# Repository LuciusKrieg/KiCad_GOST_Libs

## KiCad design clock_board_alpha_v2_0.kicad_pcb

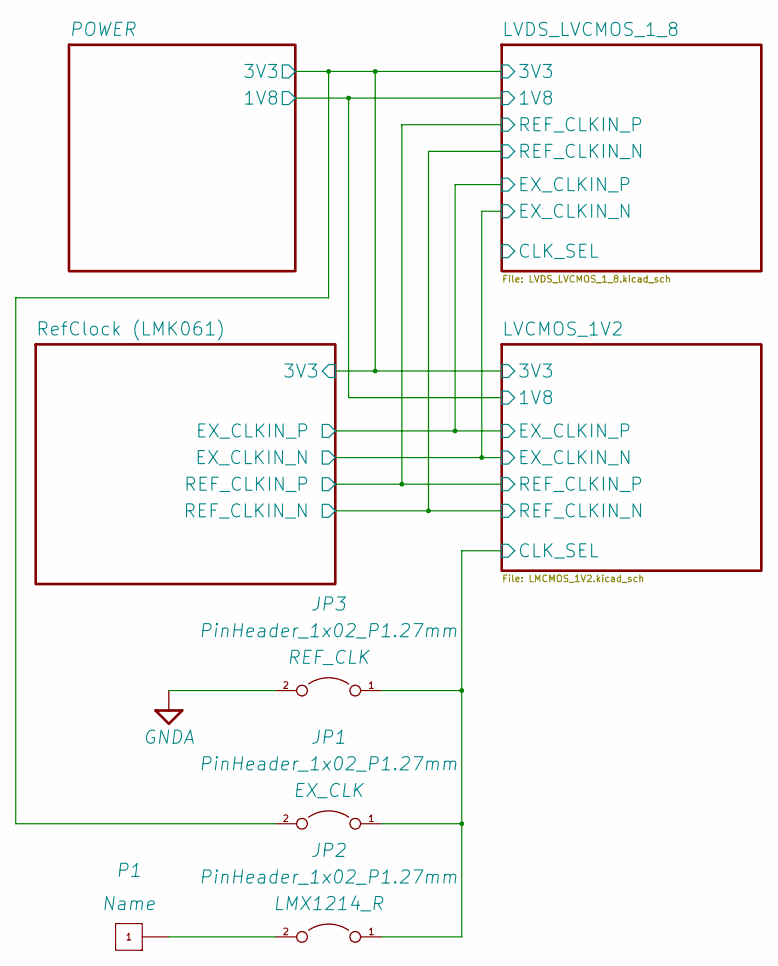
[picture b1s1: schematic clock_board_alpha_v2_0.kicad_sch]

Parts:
JP1, JP2, JP3: PinHeader_1x02_P1.27mm; PinHeader_1x02_P1.27mm_Vertical
P1: PinHeader_1x01_P1.00mm_Vertical

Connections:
/LVCMOS_1V2/CLK_SEL: JP1.1 (A), JP2.1 (A), JP3.1 (A); also elsewhere on the board
GNDA: JP3.2 (B); also elsewhere on the board
unnamed: JP2.2 (B), P1.1
VDD_3V3: JP1.2 (B); also elsewhere on the board

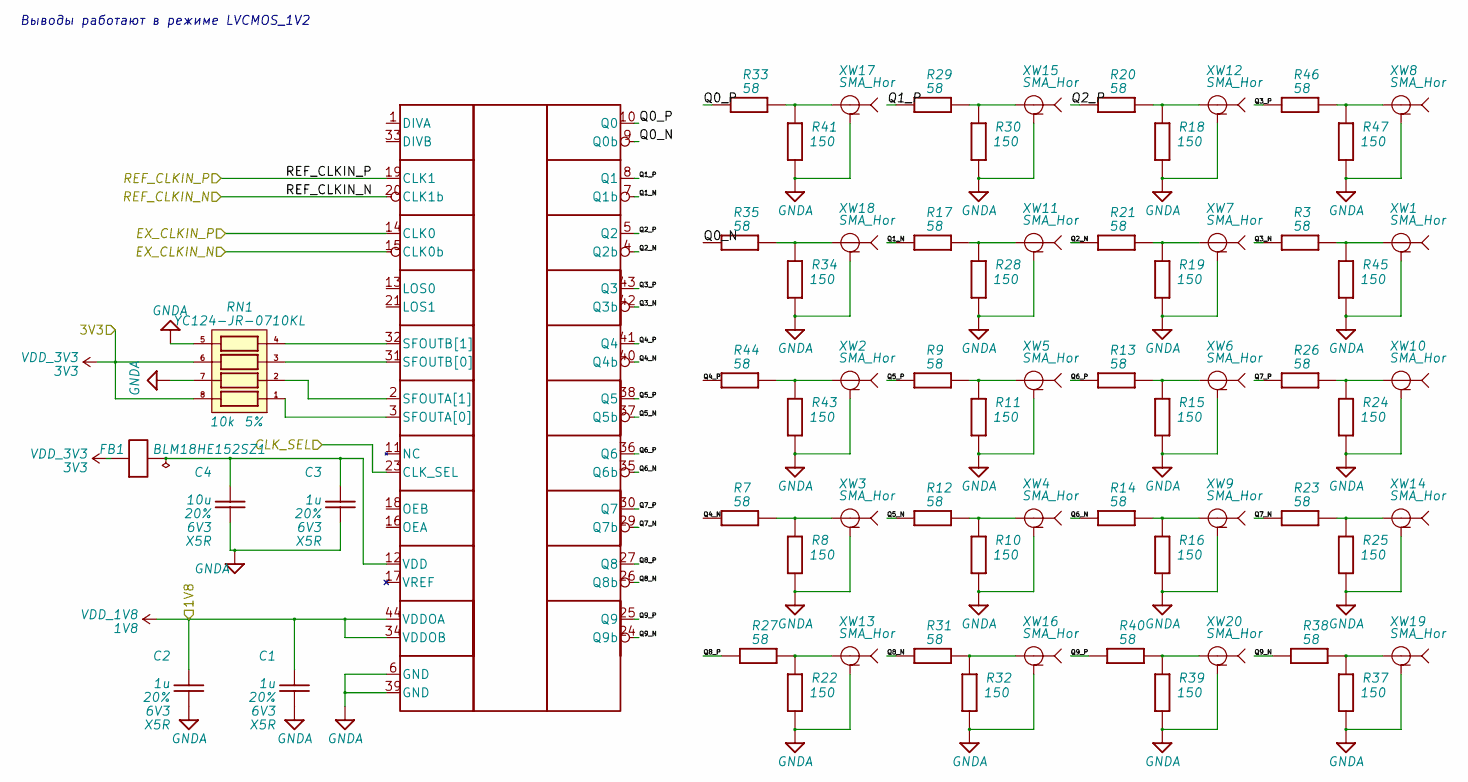
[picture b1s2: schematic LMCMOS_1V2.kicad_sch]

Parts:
C1, C2, C3: GRM033R60J105MEA; C_0201_0603Metric; Tolerance 20%
C4: CL05A106MQ5NUNC; C_0402_1005Metric; Tolerance 20%
FB1: BLM18HE152SZ1; L_0603_1608Metric
R3, R7, R8, R9, R10, R11, R12, R13, R14, R15, R16, R17, R18, R19, R20, R21, R22, R23, R24, R25, R26, R27, R28, R29, R30, R31, R32, R33, R34, R35, R37, R38, R39, R40, R41, R43, R44, R45, R46, R47: TNPR020150R0FEED; R_0201_0603Metric; Tolerance 1%
RN1: YC124-JR-0710KL; R_Array_Convex_4x0402; Tolerance 5%
SI53302: TQFN-44-1EP_7x7mm_P0.5mm_EP4.7x4.7mm
XW1, XW2, XW3, XW4, XW5, XW6, XW7, XW8, XW9, XW10, XW11, XW12, XW13, XW14, XW15, XW16, XW17, XW18, XW19, XW20: SMA_Amphenol_901-143_Horizontal

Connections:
/LVCMOS_1V2/CLK_SEL: SI53302.23 (CLK_SEL); also elsewhere on the board
/LVCMOS_1V2/Q0_N: R35.2, SI53302.9 (Q0b)
/LVCMOS_1V2/Q0_P: R33.2, SI53302.10 (Q0)
/LVCMOS_1V2/Q1_N: R17.2, SI53302.7 (Q1b)
/LVCMOS_1V2/Q1_P: R29.2, SI53302.8 (Q1)
/LVCMOS_1V2/Q2_N: R21.2, SI53302.4 (Q2b)
/LVCMOS_1V2/Q2_P: R20.2, SI53302.5 (Q2)
/LVCMOS_1V2/Q3_N: R3.2, SI53302.42 (Q3b)
/LVCMOS_1V2/Q3_P: R46.2, SI53302.43 (Q3)
/LVCMOS_1V2/Q4_N: R7.2, SI53302.40 (Q4b)
/LVCMOS_1V2/Q4_P: R44.2, SI53302.41 (Q4)
/LVCMOS_1V2/Q5_N: R12.2, SI53302.37 (Q5b)
/LVCMOS_1V2/Q5_P: R9.2, SI53302.38 (Q5)
/LVCMOS_1V2/Q6_N: R14.2, SI53302.35 (Q6b)
/LVCMOS_1V2/Q6_P: R13.2, SI53302.36 (Q6)
/LVCMOS_1V2/Q7_N: R23.2, SI53302.29 (Q7b)
/LVCMOS_1V2/Q7_P: R26.2, SI53302.30 (Q7)
/LVCMOS_1V2/Q8_N: R31.2, SI53302.26 (Q8b)
/LVCMOS_1V2/Q8_P: R27.2, SI53302.27 (Q8)
/LVCMOS_1V2/Q9_N: R38.2, SI53302.24 (Q9b)
/LVCMOS_1V2/Q9_P: R40.2, SI53302.25 (Q9)
/LVCMOS_1V2/REF_CLKIN_N: SI53302.20 (CLK1b); also elsewhere on the board
/LVCMOS_1V2/REF_CLKIN_P: SI53302.19 (CLK1); also elsewhere on the board
/RefClock (LMK061)/EX_CLKIN_N: SI53302.15 (CLK0b); also elsewhere on the board
/RefClock (LMK061)/EX_CLKIN_P: SI53302.14 (CLK0); also elsewhere on the board
GNDA: C1.2, C2.2, C3.2, C4.2, R8.1, R10.1, R11.1, R15.1, R16.1, R18.1, R19.1, R22.1, R24.1, R25.1, R28.1, R30.1, R32.1, R34.1, R37.1, R39.1, R41.1, R43.1, R45.1, R47.1, RN1.5, RN1.7, SI53302.6 (GND), SI53302.39 (GND), XW1.2, XW2.2, XW3.2, XW4.2, XW5.2, XW6.2, XW7.2, XW8.2, XW9.2, XW10.2, XW11.2, XW12.2, XW13.2, XW14.2, XW15.2, XW16.2, XW17.2, XW18.2, XW19.2, XW20.2; also elsewhere on the board
unnamed: R3.1, R45.2, XW1.1
unnamed: R7.1, R8.2, XW3.1
unnamed: R10.2, R12.1, XW4.1
unnamed: R9.1, R11.2, XW5.1
unnamed: R13.1, R15.2, XW6.1
unnamed: R14.1, R16.2, XW9.1
unnamed: R17.1, R28.2, XW11.1
unnamed: R18.2, R20.1, XW12.1
unnamed: R19.2, R21.1, XW7.1
unnamed: R22.2, R27.1, XW13.1
unnamed: R23.1, R25.2, XW14.1
unnamed: R24.2, R26.1, XW10.1
unnamed: R29.1, R30.2, XW15.1
unnamed: R31.1, R32.2, XW16.1
unnamed: R33.1, R41.2, XW17.1
unnamed: R34.2, R35.1, XW18.1
unnamed: R37.2, R38.1, XW19.1
unnamed: R39.2, R40.1, XW20.1
unnamed: R43.2, R44.1, XW2.1
unnamed: R46.1, R47.2, XW8.1
unnamed: RN1.1, SI53302.3 (SFOUTA[0])
unnamed: RN1.2, SI53302.2 (SFOUTA[1])
unnamed: RN1.3, SI53302.31 (SFOUTB[0])
unnamed: RN1.4, SI53302.32 (SFOUTB[1])
unnamed: C3.1, C4.1, FB1.2, SI53302.12 (VDD)
VDD_1V8: C1.1, C2.1, SI53302.34 (VDDOB), SI53302.44 (VDDOA); also elsewhere on the board
VDD_3V3: FB1.1, RN1.6, RN1.8; also elsewhere on the board

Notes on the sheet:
Выводы работают в режиме LVСMOS_1V2

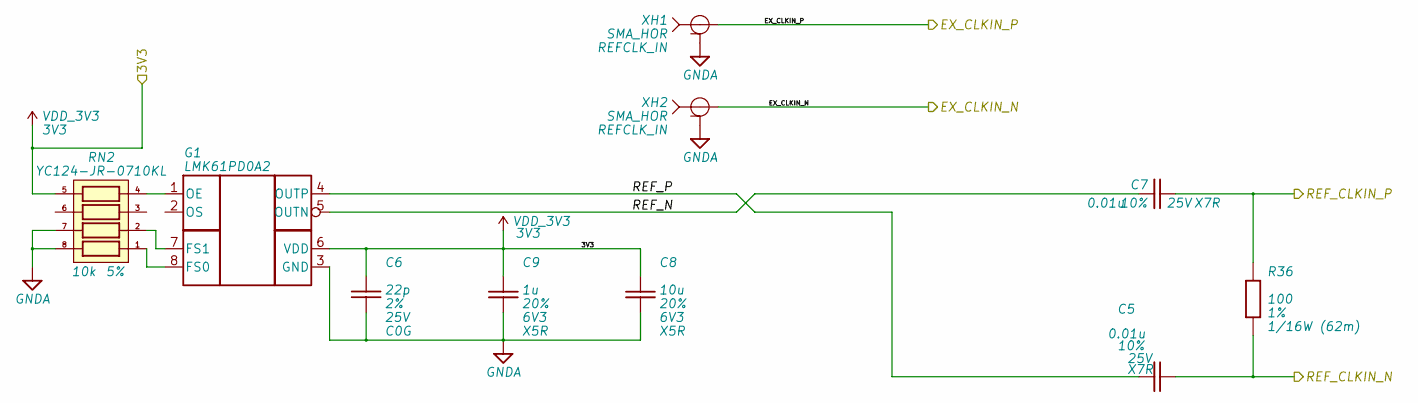
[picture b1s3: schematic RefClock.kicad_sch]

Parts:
C5, C7: GRM033R71E103KE; C_0201_0603Metric; Tolerance 10%
C6: GJM0335C1E220GB; C_0201_0603Metric; Tolerance 2%
C8: CL05A106MQ5NUNC; C_0402_1005Metric; Tolerance 20%
C9: GRM033R60J105MEA; C_0201_0603Metric; Tolerance 20%
G1: LMK61PD0A2; QFM-8-SIA
R36: RC0402FR-07100RL; R_0402_1005Metric; Tolerance 1%
RN2: YC124-JR-0710KL; R_Array_Convex_4x0402; Tolerance 5%
XH1, XH2: SMA_HOR; SMA_Amphenol_901-144_Vertical

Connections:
/LVCMOS_1V2/REF_CLKIN_N: C5.2, R36.1; also elsewhere on the board
/LVCMOS_1V2/REF_CLKIN_P: C7.2, R36.2; also elsewhere on the board
/RefClock (LMK061)/EX_CLKIN_N: XH2.1; also elsewhere on the board
/RefClock (LMK061)/EX_CLKIN_P: XH1.1; also elsewhere on the board
/RefClock (LMK061)/REF_N: C7.1, G1.5 (OUTN)
/RefClock (LMK061)/REF_P: C5.1, G1.4 (OUTP)
GNDA: C6.1, C8.2, C9.2, G1.3 (GND), RN2.7, RN2.8, XH1.2, XH2.2; also elsewhere on the board
unnamed: G1.8 (FS0), RN2.1
unnamed: G1.7 (FS1), RN2.2
unnamed: G1.1 (OE), RN2.4
VDD_3V3: C6.2, C8.1, C9.1, G1.6 (VDD), RN2.5; also elsewhere on the board

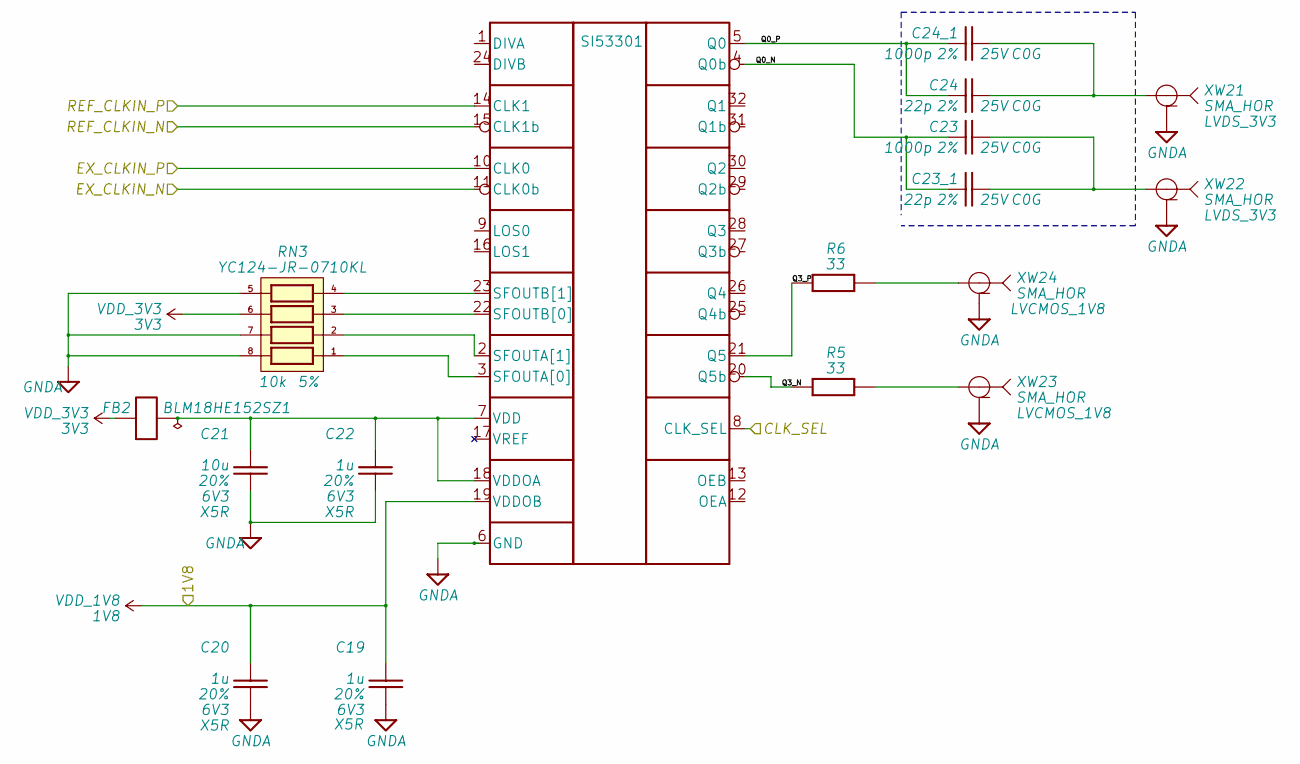
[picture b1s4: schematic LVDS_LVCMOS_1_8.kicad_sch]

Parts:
C19, C20, C22: GRM033R60J105MEA; C_0201_0603Metric; Tolerance 20%
C21: CL05A106MQ5NUNC; C_0402_1005Metric; Tolerance 20%
C23, C24_1: GRM0335C1E102GA; C_0201_0603Metric; Tolerance 2%
C23_1, C24: GJM0335C1E220GB; C_0201_0603Metric; Tolerance 2%
FB2: BLM18HE152SZ1; L_0603_1608Metric
R5, R6: TNPR020150R0FEED; R_0201_0603Metric; Tolerance 1%
RN3: YC124-JR-0710KL; R_Array_Convex_4x0402; Tolerance 5%
SI53301: QFN-32-1EP_5x5mm_P0.5mm_EP3.1x3.1mm
XW21, XW22, XW23, XW24: SMA_HOR; SMA_Amphenol_901-143_Horizontal

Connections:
/LVCMOS_1V2/REF_CLKIN_N: SI53301.15 (CLK1b); also elsewhere on the board
/LVCMOS_1V2/REF_CLKIN_P: SI53301.14 (CLK1); also elsewhere on the board
/LVDS_LVCMOS_1_8/CLK_SEL: SI53301.8 (CLK_SEL)
/LVDS_LVCMOS_1_8/Q0_N: C23.1, C23_1.1, SI53301.4 (Q0b)
/LVDS_LVCMOS_1_8/Q0_P: C24.1, C24_1.1, SI53301.5 (Q0)
/LVDS_LVCMOS_1_8/Q3_N: R5.2, SI53301.20 (Q5b)
/LVDS_LVCMOS_1_8/Q3_P: R6.2, SI53301.21 (Q5)
/RefClock (LMK061)/EX_CLKIN_N: SI53301.11 (CLK0b); also elsewhere on the board
/RefClock (LMK061)/EX_CLKIN_P: SI53301.10 (CLK0); also elsewhere on the board
GNDA: C19.2, C20.2, C21.2, C22.2, RN3.5, RN3.7, RN3.8, SI53301.6 (GND), XW21.2, XW22.2, XW23.2, XW24.2; also elsewhere on the board
unnamed: C23.2, C23_1.2, XW22.1
unnamed: C24.2, C24_1.2, XW21.1
unnamed: R5.1, XW23.1
unnamed: R6.1, XW24.1
unnamed: RN3.1, SI53301.3 (SFOUTA[0])
unnamed: RN3.2, SI53301.2 (SFOUTA[1])
unnamed: RN3.3, SI53301.22 (SFOUTB[0])
unnamed: RN3.4, SI53301.23 (SFOUTB[1])
unnamed: C21.1, C22.1, FB2.2, SI53301.7 (VDD), SI53301.18 (VDDOA)
VDD_1V8: C19.1, C20.1, SI53301.19 (VDDOB); also elsewhere on the board
VDD_3V3: FB2.1, RN3.6; also elsewhere on the board

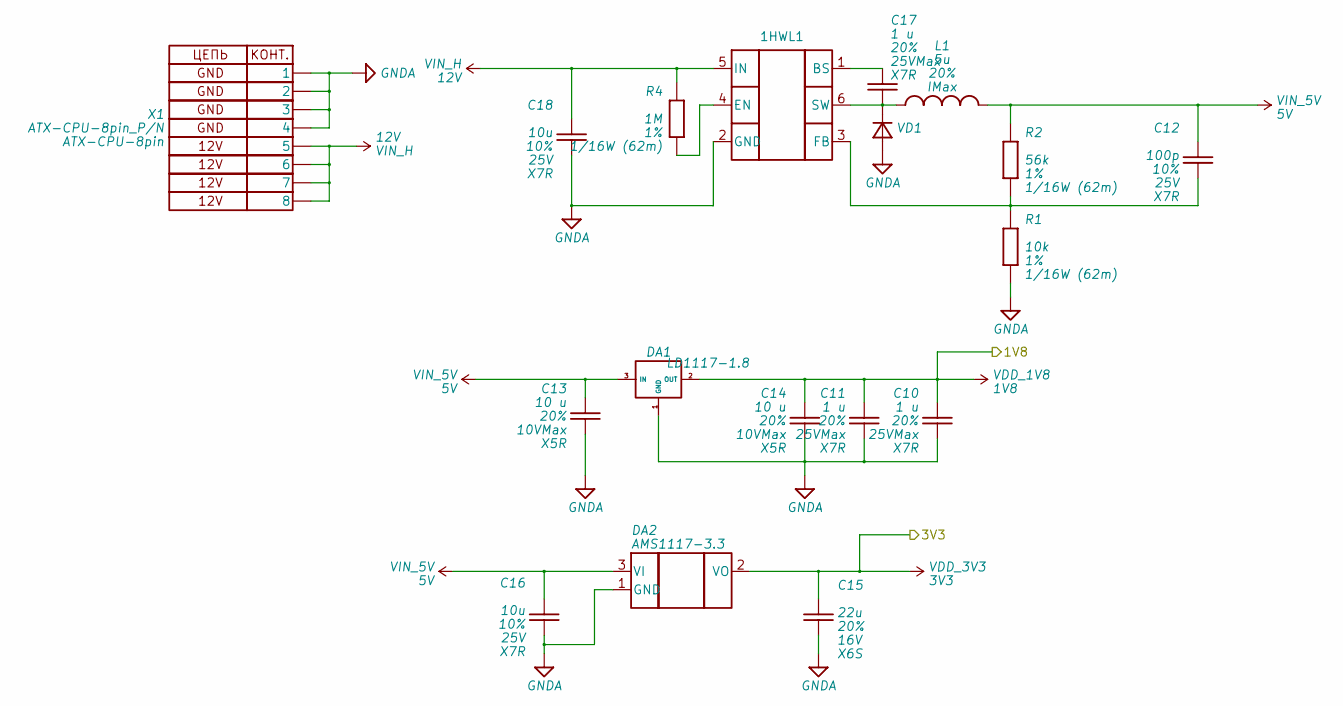
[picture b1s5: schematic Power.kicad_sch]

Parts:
1HWL1: SOT-23-6
C10, C11, C17: GRM155R61E105KA12D; C_0201_0603Metric; Tolerance 20%
C12, C16, C18: CL21B106KAYQNN; C_0805_2012Metric; Tolerance 10%
C13, C14: CL05A106MP5NUNC; C_0402_1005Metric; Tolerance 20%
C15: GRM21BC81C226ME44; C_0805_2012Metric; Tolerance 20%
DA1: LD1117-1.8; SOT-223-3_TabPin2
DA2: AMS1117-3.3; SOT-223-3_TabPin2
L1: L_Wuerth_HCI-5040; Tolerance 20%
R1: RC0402FR-074K87L; R_0402_1005Metric; Tolerance 1%
R2: RC0402FR-0720KL; R_0402_1005Metric; Tolerance 1%
R4: RC0402FR-0742K2L; R_0402_1005Metric; Tolerance 1%
VD1: D_0402_1005Metric
X1: ATX-CPU-8pin_P/N; Molex_Mini-Fit_Jr_5566-08A_2x04_P4.20mm_Vertical

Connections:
GNDA: 1HWL1.2 (GND), C10.2, C11.2, C13.2, C14.2, C15.2, C16.2, C18.2, DA1.1 (GND), DA2.1 (GND), R1.1, VD1.2 (A), X1.1, X1.2, X1.3, X1.4; also elsewhere on the board
unnamed: 1HWL1.1 (BS), C17.1
unnamed: 1HWL1.4 (EN), R4.1
unnamed: 1HWL1.3 (FB), C12.2, R1.2, R2.1
unnamed: 1HWL1.6 (SW), C17.2, L1.1, VD1.1 (K)
VDD_1V8: C10.1, C11.1, C14.1, DA1.2 (OUT); also elsewhere on the board
VDD_3V3: C15.1, DA2.2 (VO); also elsewhere on the board
VIN_5V: C12.1, C13.1, C16.1, DA1.3 (IN), DA2.3 (VI), L1.2, R2.2
VIN_H: 1HWL1.5 (IN), C18.1, R4.2, X1.5, X1.6, X1.7, X1.8

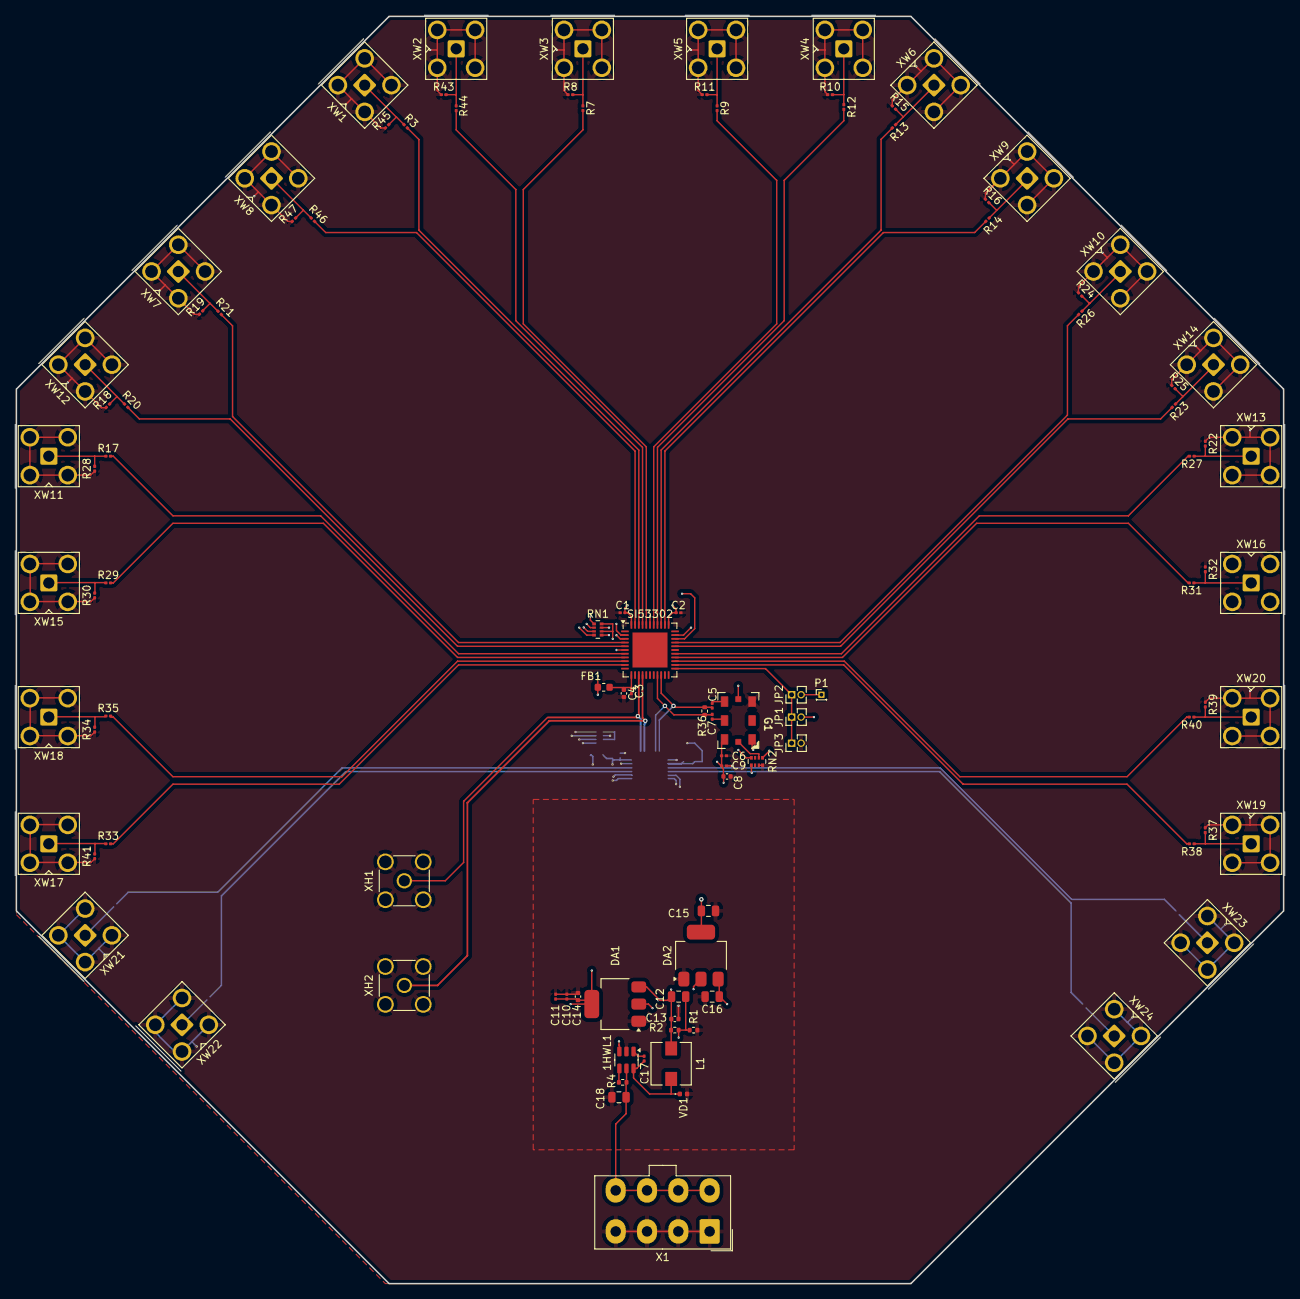
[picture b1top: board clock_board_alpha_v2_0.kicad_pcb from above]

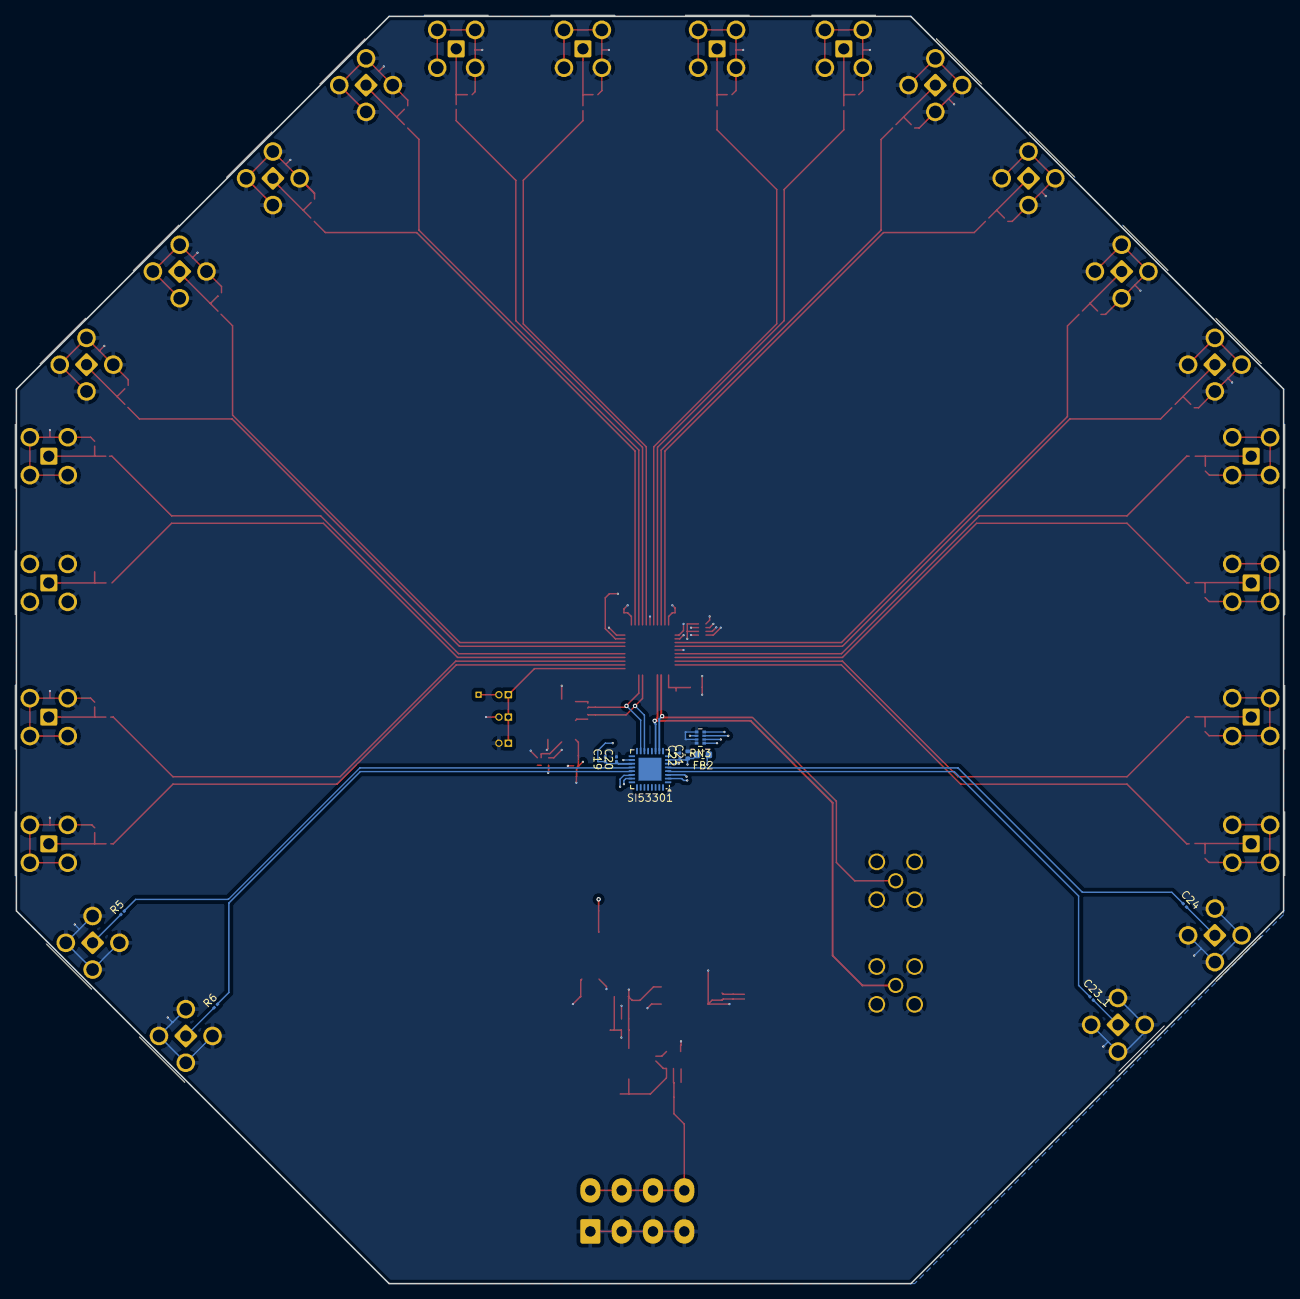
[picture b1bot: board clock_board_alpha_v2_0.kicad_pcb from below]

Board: 4 copper layers, 170.2 x 170.1 mm, 114 parts (11 on the bottom side), 78 nets.

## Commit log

2025-06-30 Added new GOST_Lib
